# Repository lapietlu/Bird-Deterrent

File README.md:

# Bird-Deterrent
Files related to the iterative design of the Audio Bird Deterrent, for online access and reference. 

This holds the Arduino project files, with folders holding the last edit to a current version. These versions mark milestone updates in the software, and are differentiated by that functionality. Small patches are updated locally, and won't be published to this repository. 

GERBER files for the circuit board are included for viewing here as well.

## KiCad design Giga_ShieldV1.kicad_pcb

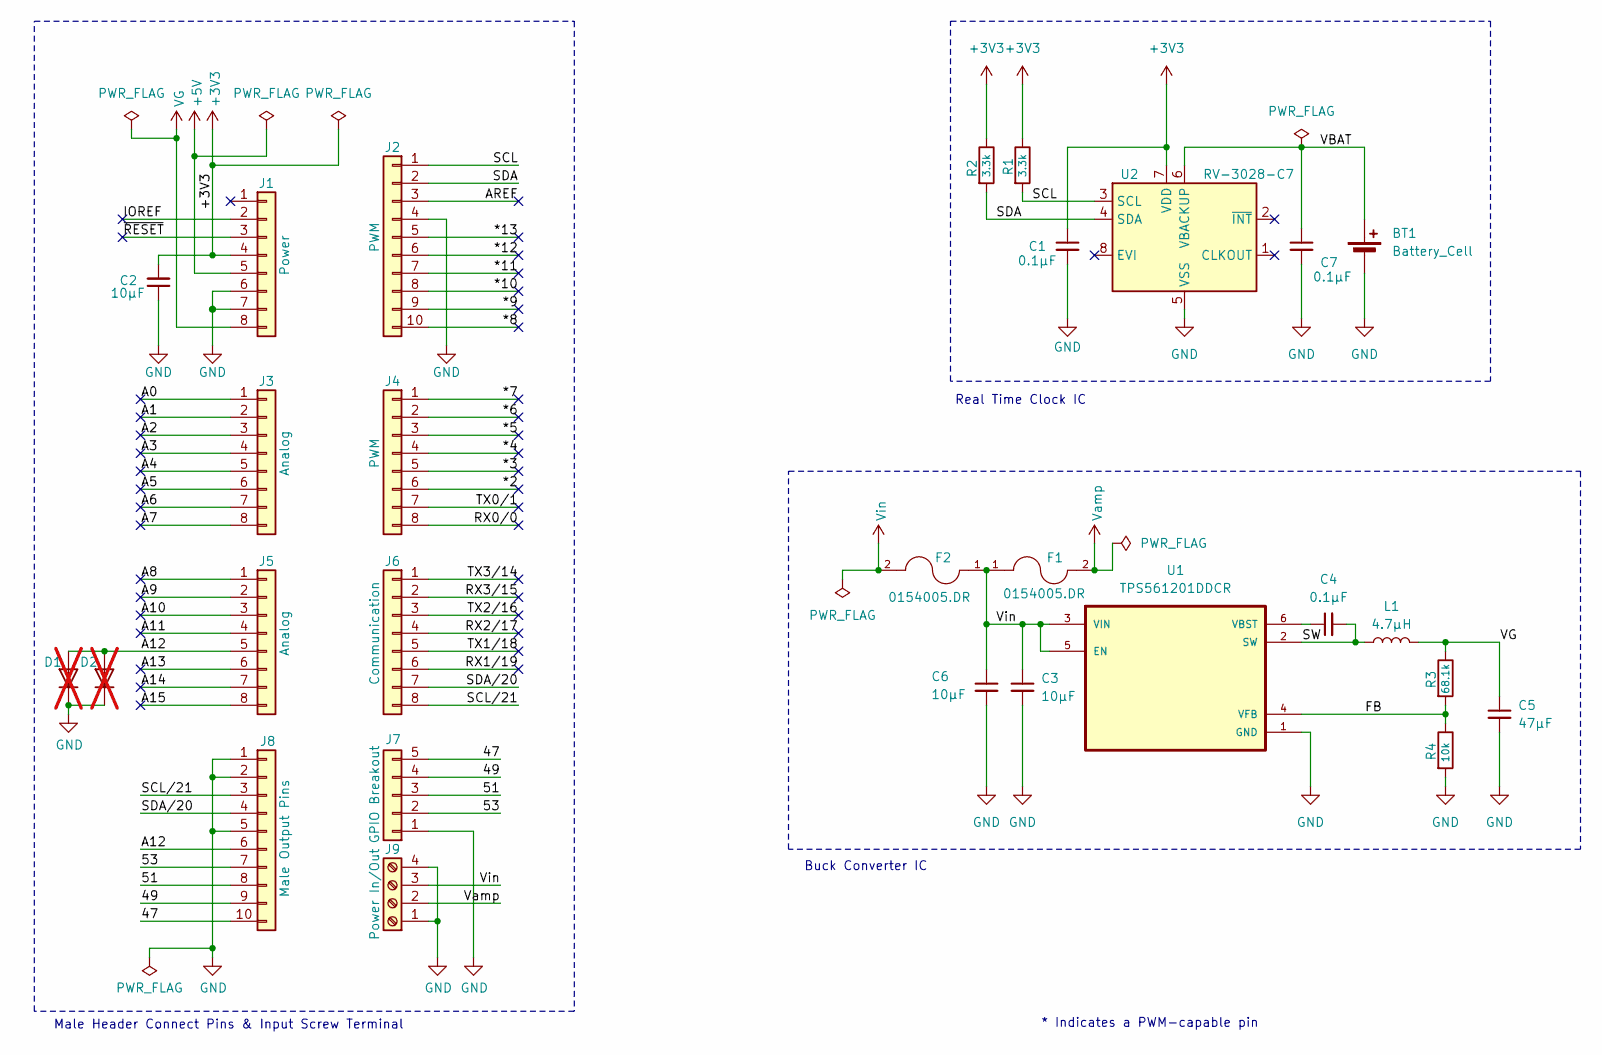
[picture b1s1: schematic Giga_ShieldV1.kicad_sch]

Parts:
BT1: Battery_Cell; BatteryHolder_Keystone_1060_1x2032
C1, C4, C7: 0.1µF; C_0805_2012Metric
C2, C3, C6: 10µF; C_0805_2012Metric
C5: 47µF; CAPC3225X270N
D1, D2: 1N4148WT; D_MELF-RM10_Universal_Handsoldering; not fitted
F1, F2: 0154005.DR; FUSE_0154005.DR; PARTREV GD
J1: Power; PinHeader_1x08_P2.54mm_Vertical
J2: PWM; PinHeader_1x10_P2.54mm_Vertical
J3, J5: Analog; PinHeader_1x08_P2.54mm_Vertical
J4: PWM; PinHeader_1x08_P2.54mm_Vertical
J6: Communication; PinHeader_1x08_P2.54mm_Vertical
J7: GPIO Breakout; PinHeader_1x05_P2.54mm_Vertical
J8: Male Output Pins; PinHeader_1x10_P2.54mm_Vertical
J9: Power In/Out; TerminalBlock_Phoenix_MPT-0,5-4-2.54_1x04_P2.54mm_Horizontal
L1: 4.7µH; WE-LQS_5040
R1, R2: 3.3k; R_0402_1005MetricWORK
R3: 68.1k; R_0402_1005Metric
R4: 10k; R_0402_1005Metric
U1: TPS561201DDCR; SOT95P280X110-6N
U2: RV-3028-C7; MicroCrystal_C7_SON-8_1.5x3.2mm_P0.9mm

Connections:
+3V3: C1.1, C2.2, J1.4, R1.1, R2.1, U2.7 (VDD)
+5V: J1.5
/47: J7.5, J8.10
/49: J7.4, J8.9
/51: J7.3, J8.8
/53: J7.2, J8.7
/*2: J4.6
/*3: J4.5
/*4: J4.4
/*5: J4.3
/*6: J4.2
/*7: J4.1
/*8: J2.10
/*9: J2.9
/*10: J2.8
/*11: J2.7
/*12: J2.6
/*13: J2.5
/A0: J3.1
/A1: J3.2
/A2: J3.3
/A3: J3.4
/A4: J3.5
/A5: J3.6
/A6: J3.7
/A7: J3.8
/A8: J5.1
/A9: J5.2
/A10: J5.3
/A11: J5.4
/A12: D1.2 (A), D2.2 (A), J5.5, J8.6
/A13: J5.6
/A14: J5.7
/A15: J5.8
/AREF: J2.3
/FB: R3.2, R4.1, U1.4 (VFB)
/IOREF: J1.2
/RX0/0: J4.8
/RX1/19: J6.6
/RX2/17: J6.4
/RX3/15: J6.2
/SCL: J2.1, R1.2, U2.3 (SCL)
/SCL/21: J6.8, J8.3
/SDA: J2.2, R2.2, U2.4 (SDA)
/SDA/20: J6.7, J8.4
/SW: C4.2, L1.1, U1.2 (SW)
/TX0/1: J4.7
/TX1/18: J6.5
/TX2/16: J6.3
/TX3/14: J6.1
/VBAT: BT1.1 (+), C7.1, U2.6 (VBACKUP)
/~RESET: J1.3
GND: BT1.2 (-), C1.2, C2.1, C3.2, C5.2, C6.2, C7.2, D1.1 (K), D2.1 (K), J1.6, J1.7, J2.4, J7.1, J8.1, J8.2, J8.5, J9.1, J9.4, R4.2, U1.1 (GND), U2.5 (VSS)
unnamed: C4.1, U1.6 (VBST)
VG: C5.1, J1.8, L1.2, R3.1
Vamp: F1.2, J9.2
Vin: C3.1, C6.1, F1.1, F2.1, F2.2, J9.3, U1.3 (VIN), U1.5 (EN)

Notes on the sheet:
Buck Converter IC
Male Header Connect Pins & Input Screw Terminal
* Indicates a PWM-capable pin
Real Time Clock IC

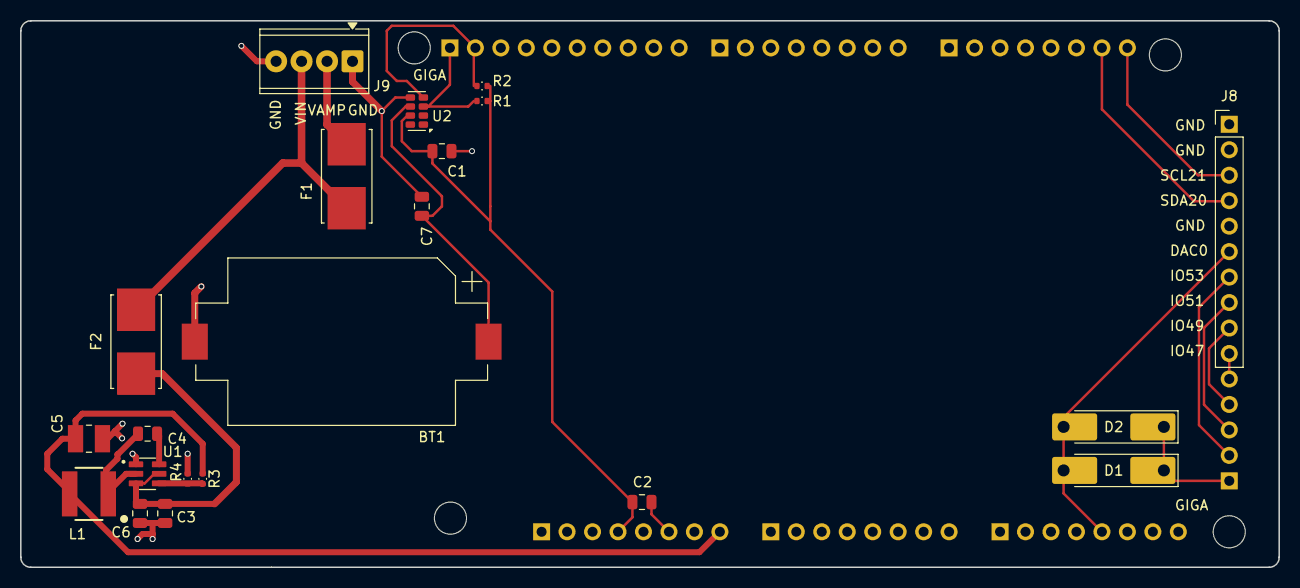
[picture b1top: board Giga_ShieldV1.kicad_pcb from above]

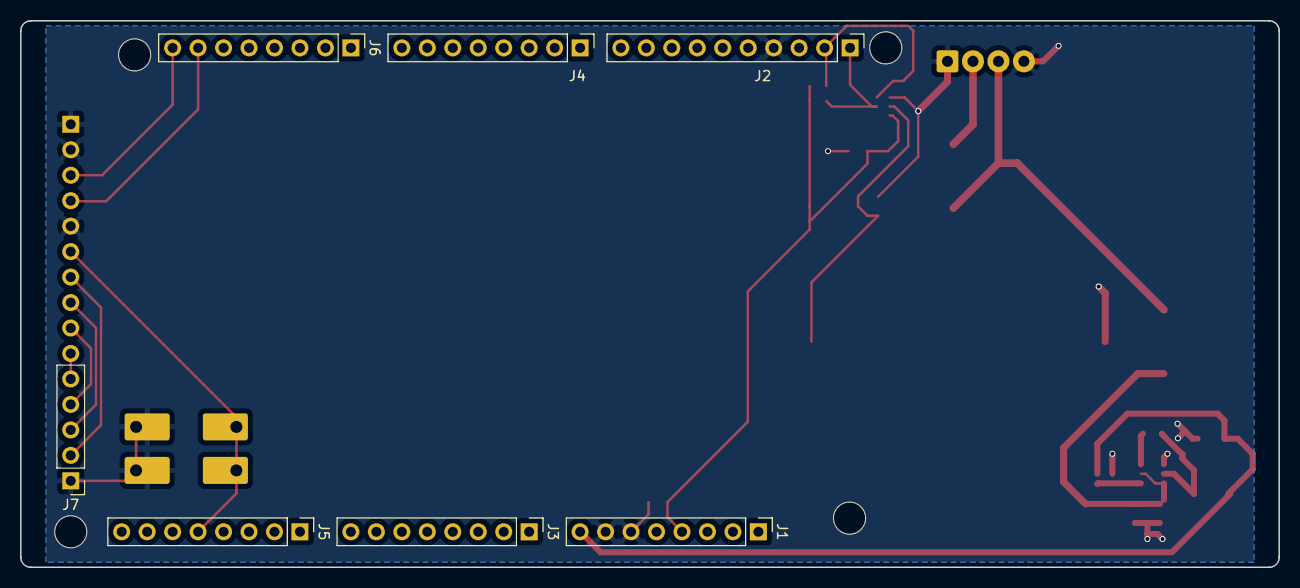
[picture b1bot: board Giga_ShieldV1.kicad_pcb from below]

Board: 2 copper layers, 125.5 x 54.5 mm, 32 parts (7 on the bottom side), 18 nets.

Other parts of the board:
MH1, MH2, MH5, MH6: MountingHole_3.2mm

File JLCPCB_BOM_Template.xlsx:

Comment | Designator | Footprint | JLCPCB Part#(optional)
TI Buck IC | U1 | TSOT-23-6 | C220433
MC RTC | U2 | SMD3215-8P | C3019759
4.7uH 3A 39DCR | L1 | SMD,5x5mm | C1331933
10uF 25V Ceramic X5R | C2, C3, C6 | 805.0 | C391262
47uF 10V Ceramic X7R | C5 | 1210.0 | C84494
0.1uF 50V Ceramnic X7R | C1, C4, C7 | 805.0 | C92849
3.3kΩ 50V 63mW Thick +-1 | R1, R2 | 402.0 | C482167
50V 62.5mW 68.1kΩ Thick +-1 | R3 | 402.0 | C844116
10kΩ 50V 62.5mW Thick +-1 | R4 | 402.0 | C844714
Keystone 1060TR 2032 | BT1 | Special | C238069
2.54mm 8-Pin Header | J1 | Plugin,P=2.54mm | C2337 | ???
2.54mm 10-Pin Header | J2 | Plugin,P=2.54mm | C2337 | ???
2.54mm 8-Pin Header | J3 | Plugin,P=2.54mm | C2337 | ???
2.54mm 8-Pin Header | J4 | Plugin,P=2.54mm | C2337 | ???
2.54mm 8-Pin Header | J5 | Plugin,P=2.54mm | C2337 | ???
2.54mm 8-Pin Header | J6 | Plugin,P=2.54mm | C2337 | ???
2.54mm 5-Pin Header | J7 | Plugin,P=2.54mm | C2337 | ???
2.54mm 10-Pin Header | J8 | Plugin,P=2.54mm | C2337 | ???
4-Pin Screw Terminal | J9 | Plugin,P=2.54mm | C3816889
Fuse Slot | F1 | SMD,9.7x5mm | C206916
Fuse Slot | F2 | SMD,9.7x5mm | C206916
Do Not Populate | D1, D2 | Included in Sent Files | DNE

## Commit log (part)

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2026-05-02 Version 3.4
2026-05-02 Circuit Board Files
2026-05-07 Rename BirdDeterrnetV3.4.ino to BirdDeterrentV3.4.ino
2026-05-12 Updated Source Files
    Minor change with wav playback API misspelling.
2026-05-12 Delete BirdDeterrnetV3.4 directory
    Old file removal
2026-06-10 Added In-Browser Playback
    Implemented the lacking features for in-browser playback from the "Test" and "Play" buttons. Cleanly stops current playback, and is accomplished through a simple new /POST request implementing the sa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
